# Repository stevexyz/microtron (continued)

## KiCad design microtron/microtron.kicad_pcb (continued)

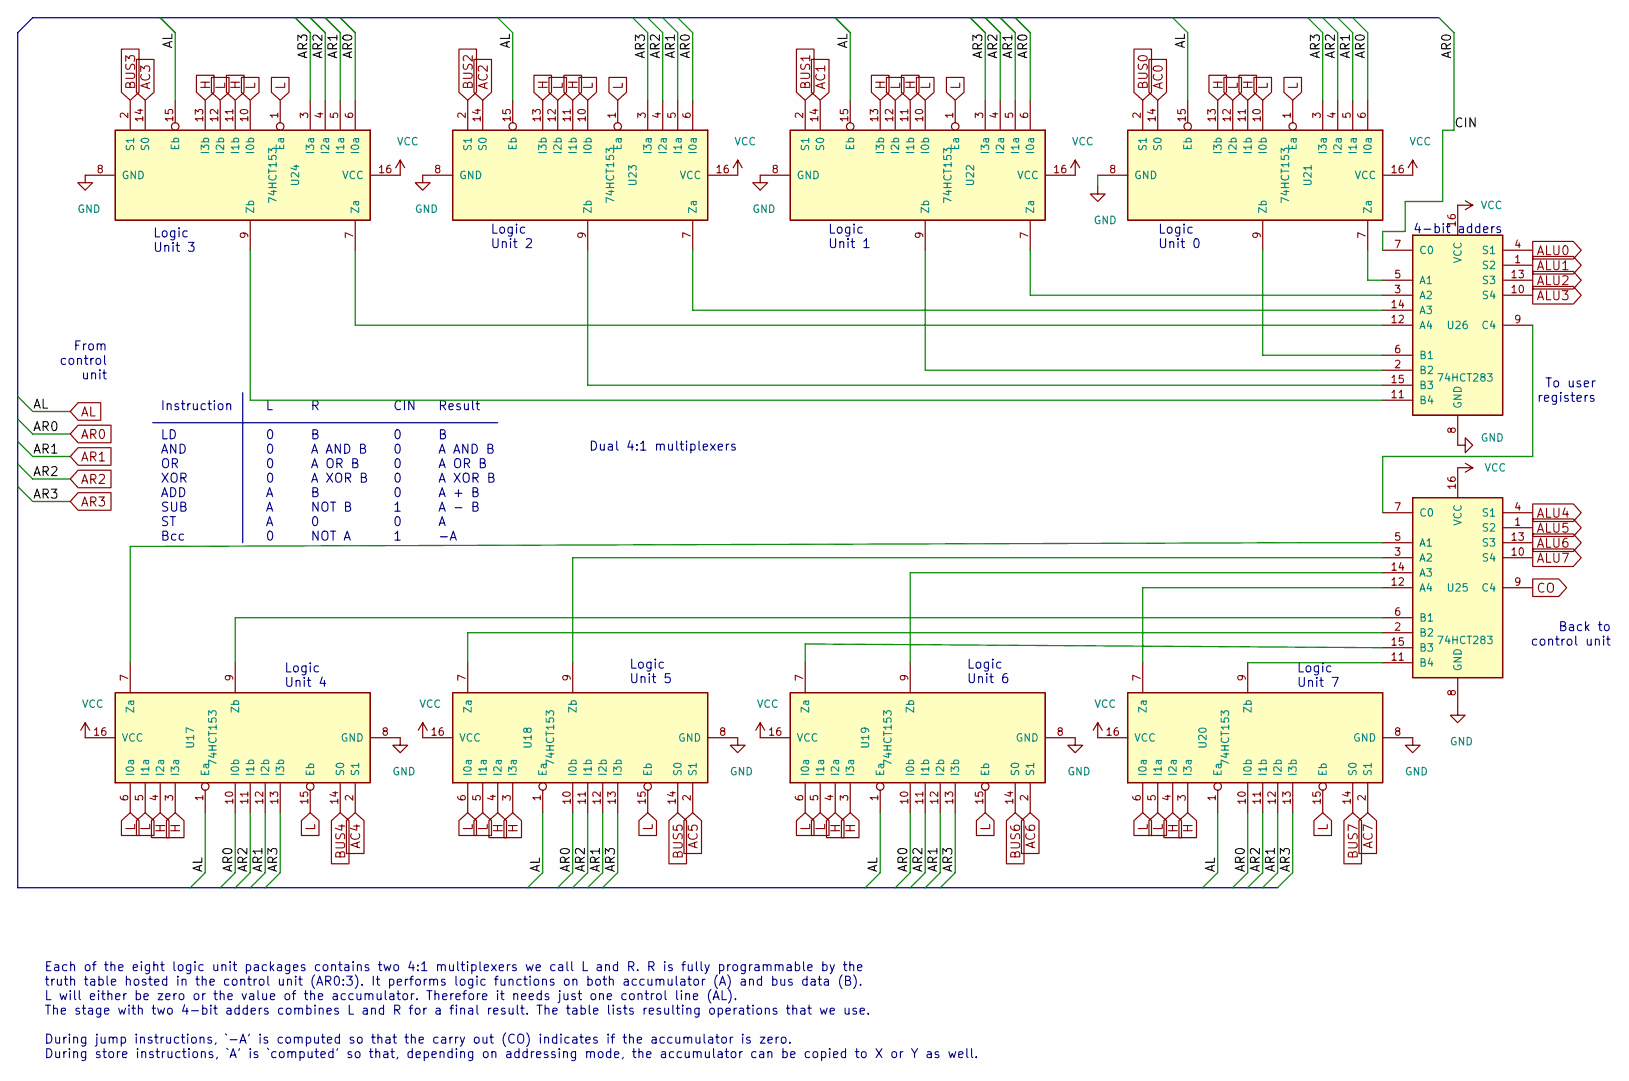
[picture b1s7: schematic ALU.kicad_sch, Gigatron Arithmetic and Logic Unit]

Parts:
U17, U18, U19, U20, U21, U22, U23, U24: 74HCT153; DIP-16_W7.62mm
U25, U26: 74HCT283; DIP-16_W7.62mm

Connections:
AC0: U21.14 (S0); also elsewhere on the board
AC1: U22.14 (S0); also elsewhere on the board
AC2: U23.14 (S0); also elsewhere on the board
AC3: U24.14 (S0); also elsewhere on the board
AC4: U17.2 (S1); also elsewhere on the board
AC5: U18.2 (S1); also elsewhere on the board
AC6: U19.2 (S1); also elsewhere on the board
AC7: U20.2 (S1); also elsewhere on the board
AL: U17.1 (Ea), U18.1 (Ea), U19.1 (Ea), U20.1 (Ea), U21.15 (Eb), U22.15 (Eb), U23.15 (Eb), U24.15 (Eb); also elsewhere on the board
ALU0: U26.4 (S1); also elsewhere on the board
ALU1: U26.1 (S2); also elsewhere on the board
ALU2: U26.13 (S3); also elsewhere on the board
ALU3: U26.10 (S4); also elsewhere on the board
ALU4: U25.4 (S1); also elsewhere on the board
ALU5: U25.1 (S2); also elsewhere on the board
ALU6: U25.13 (S3); also elsewhere on the board
ALU7: U25.10 (S4); also elsewhere on the board
AR0: U17.10 (I0b), U18.10 (I0b), U19.10 (I0b), U20.10 (I0b), U21.6 (I0a), U22.6 (I0a), U23.6 (I0a), U24.6 (I0a), U26.7 (C0); also elsewhere on the board
AR1: U17.12 (I2b), U18.12 (I2b), U19.12 (I2b), U20.12 (I2b), U21.5 (I1a), U22.5 (I1a), U23.5 (I1a), U24.5 (I1a); also elsewhere on the board
AR2: U17.11 (I1b), U18.11 (I1b), U19.11 (I1b), U20.11 (I1b), U21.4 (I2a), U22.4 (I2a), U23.4 (I2a), U24.4 (I2a); also elsewhere on the board
AR3: U17.13 (I3b), U18.13 (I3b), U19.13 (I3b), U20.13 (I3b), U21.3 (I3a), U22.3 (I3a), U23.3 (I3a), U24.3 (I3a); also elsewhere on the board
BUS0: U21.2 (S1); also elsewhere on the board
BUS1: U22.2 (S1); also elsewhere on the board
BUS2: U23.2 (S1); also elsewhere on the board
BUS3: U24.2 (S1); also elsewhere on the board
BUS4: U17.14 (S0); also elsewhere on the board
BUS5: U18.14 (S0); also elsewhere on the board
BUS6: U19.14 (S0); also elsewhere on the board
BUS7: U20.14 (S0); also elsewhere on the board
CO: U25.9 (C4); also elsewhere on the board
GND: U17.8 (GND), U18.8 (GND), U19.8 (GND), U20.8 (GND), U21.8 (GND), U22.8 (GND), U23.8 (GND), U24.8 (GND), U25.8 (GND), U26.8 (GND); also elsewhere on the board
H: U17.3 (I3a), U17.4 (I2a), U18.3 (I3a), U18.4 (I2a), U19.3 (I3a), U19.4 (I2a), U20.3 (I3a), U20.4 (I2a), U21.11 (I1b), U21.13 (I3b), U22.11 (I1b), U22.13 (I3b), U23.11 (I1b), U23.13 (I3b), U24.11 (I1b), U24.13 (I3b); also elsewhere on the board
L: U17.5 (I1a), U17.6 (I0a), U17.15 (Eb), U18.5 (I1a), U18.6 (I0a), U18.15 (Eb), U19.5 (I1a), U19.6 (I0a), U19.15 (Eb), U20.5 (I1a), U20.6 (I0a), U20.15 (Eb), U21.1 (Ea), U21.10 (I0b), U21.12 (I2b), U22.1 (Ea), U22.10 (I0b), U22.12 (I2b), U23.1 (Ea), U23.10 (I0b), U23.12 (I2b), U24.1 (Ea), U24.10 (I0b), U24.12 (I2b); also elsewhere on the board
unnamed: U17.7 (Za), U25.5 (A1)
unnamed: U17.9 (Zb), U25.6 (B1)
unnamed: U18.7 (Za), U25.2 (B2)
unnamed: U18.9 (Zb), U25.3 (A2)
unnamed: U19.7 (Za), U25.15 (B3)
unnamed: U19.9 (Zb), U25.14 (A3)
unnamed: U20.7 (Za), U25.12 (A4)
unnamed: U20.9 (Zb), U25.11 (B4)
unnamed: U21.7 (Za), U26.5 (A1)
unnamed: U21.9 (Zb), U26.6 (B1)
unnamed: U22.7 (Za), U26.3 (A2)
unnamed: U22.9 (Zb), U26.2 (B2)
unnamed: U23.7 (Za), U26.14 (A3)
unnamed: U23.9 (Zb), U26.15 (B3)
unnamed: U24.7 (Za), U26.12 (A4)
unnamed: U24.9 (Zb), U26.11 (B4)
unnamed: U25.7 (C0), U26.9 (C4)
VCC: U17.16 (VCC), U18.16 (VCC), U19.16 (VCC), U20.16 (VCC), U21.16 (VCC), U22.16 (VCC), U23.16 (VCC), U24.16 (VCC), U25.16 (VCC), U26.16 (VCC); also elsewhere on the board

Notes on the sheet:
Logic Unit 7
Back to control unit
Logic Unit 1
Logic Unit 0
Dual 4:1 multiplexers
Result B A AND B A OR B A XOR B A + B A - B A -A
Logic Unit 6
Logic Unit 2
From control unit
Instruction LD AND OR XOR ADD SUB ST Bcc
R B A AND B A OR B A XOR B B NOT B 0 NOT A
CIN 0 0 0 0 0 1 0 1
Logic Unit 4
Each of the eight logic unit packages contains two 4:1 multiplexers we call L and R. R is fully programmable by the truth table hosted in the control unit (AR0:3). It performs logic functions on both accumulator (A) and bus data (B). L will either be zero or the value of the accumulator. Therefore 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
To user registers
L 0 0 0 0 A A A 0
Logic Unit 5
4-bit adders
Logic Unit 3

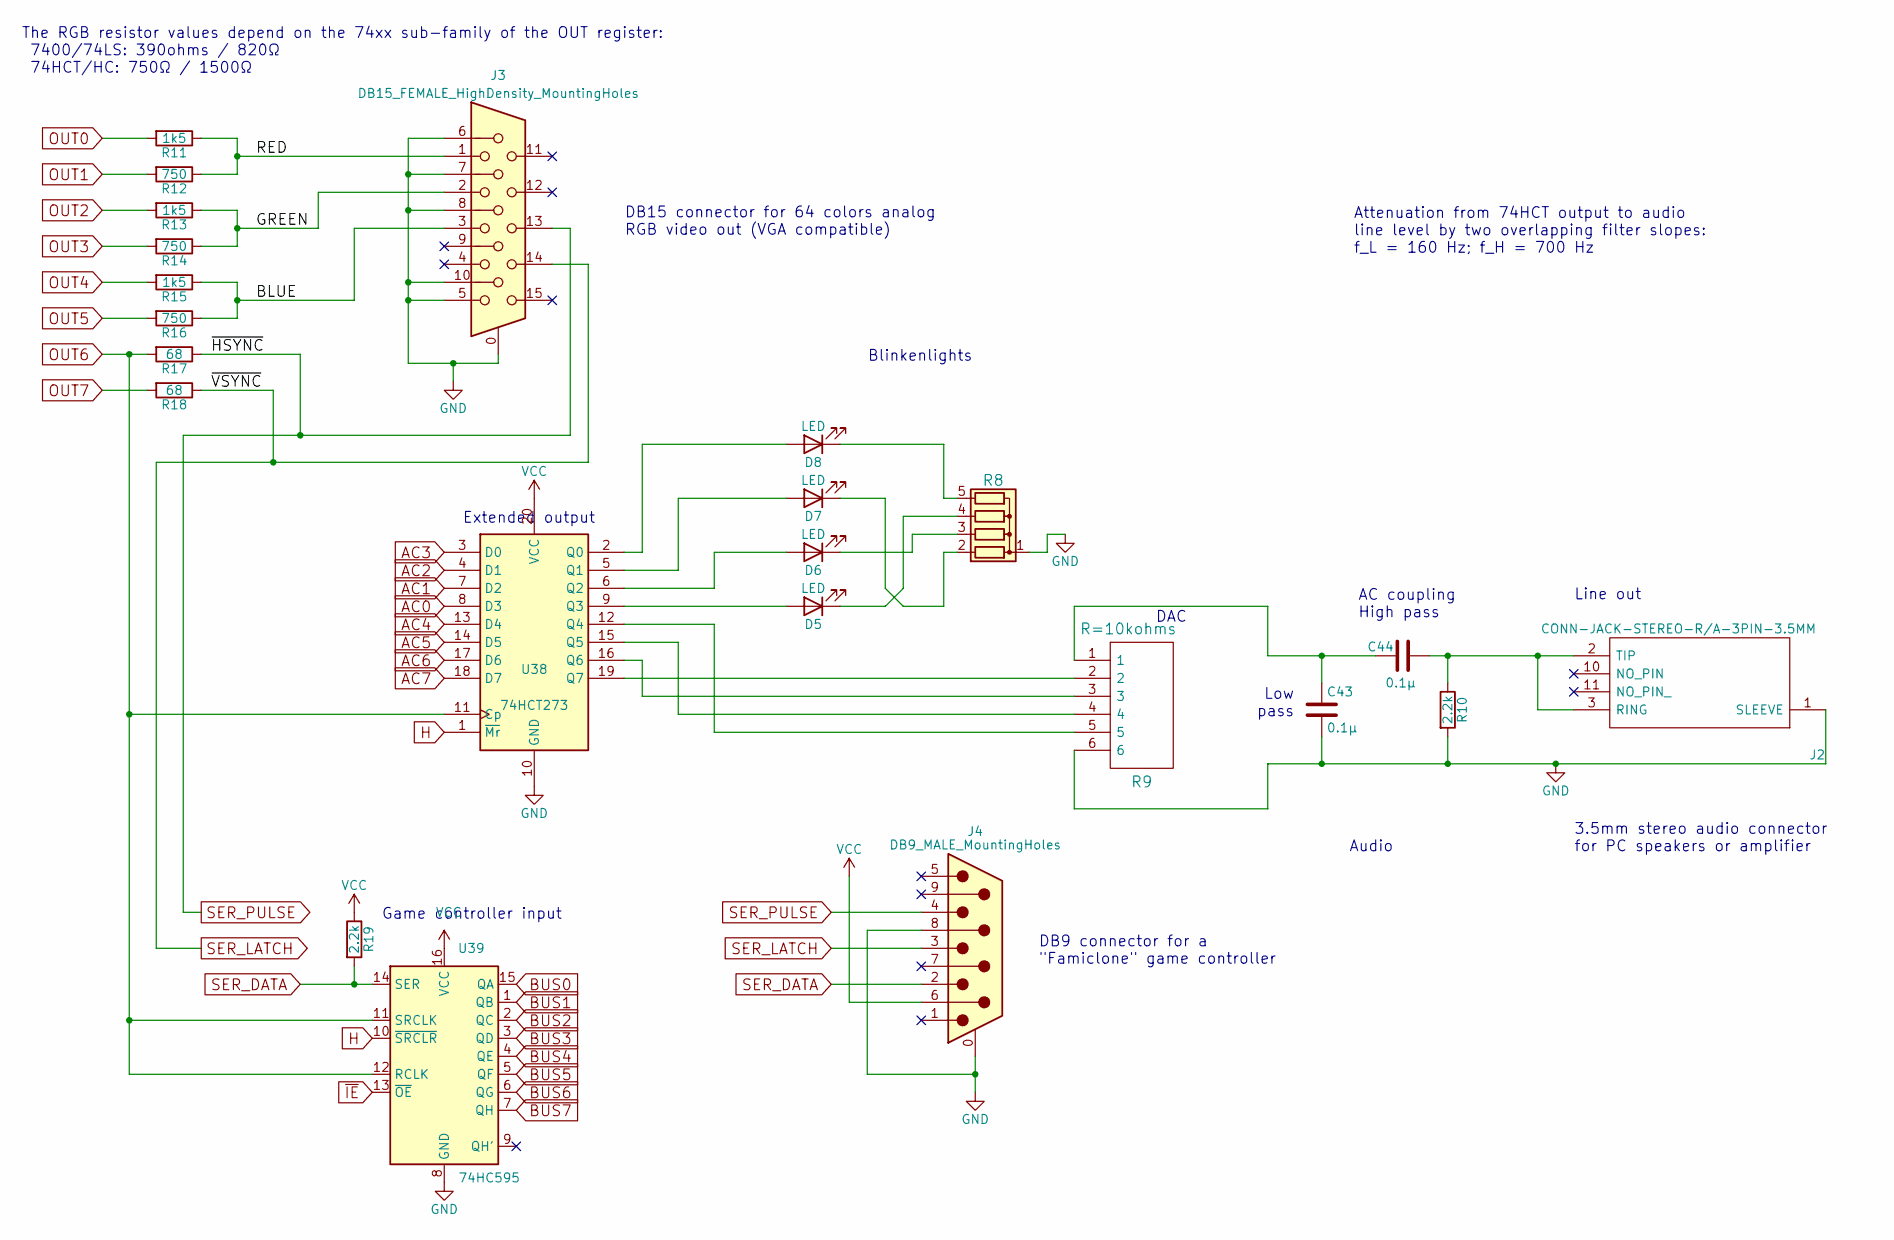
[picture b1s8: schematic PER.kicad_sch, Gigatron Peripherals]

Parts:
C43, C44: 0.1µ; C_Disc_D4.3mm_W1.9mm_P5.00mm
D5, D6, D7, D8: LED; LED_D3.0mm
J2: CONN-JACK-STEREO-R/A-3PIN-3.5MM; SJ13523N
J3: DB15_FEMALE_HighDensity_MountingHoles; DSUB-15-HD_Female_Horizontal_P2.29x1.98mm_EdgePinOffset3.03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
J4: DB9_MALE_MountingHoles; DSUB-9_Female_Horizontal_P2.77x2.84mm_EdgePinOffset4.94mm_H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
R8: 4605X-101-222LF; R_Array_SIP5
R9: R=10kohms; R_Array_SIP6
R10, R19: 2.2k; R_Axial_DIN0207_L6.3mm_D2.5mm_P10.16mm_Horizontal
R11, R13, R15: 1k5; R_Axial_DIN0207_L6.3mm_D2.5mm_P10.16mm_Horizontal
R12, R14, R16: 750; R_Axial_DIN0207_L6.3mm_D2.5mm_P10.16mm_Horizontal
R17, R18: 68; R_Axial_DIN0207_L6.3mm_D2.5mm_P10.16mm_Horizontal
U38: 74HCT273; DIP-20_W7.62mm
U39: 74HC595; DIP-16_W7.62mm

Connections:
/PER/BLUE: J3.3, R15.1, R16.1
/PER/GREEN: J3.2, R13.1, R14.1
/PER/RED: J3.1, R11.1, R12.1
AC0: U38.8 (D3); also elsewhere on the board
AC1: U38.7 (D2); also elsewhere on the board
AC2: U38.4 (D1); also elsewhere on the board
AC3: U38.3 (D0); also elsewhere on the board
AC4: U38.13 (D4); also elsewhere on the board
AC5: U38.14 (D5); also elsewhere on the board
AC6: U38.17 (D6); also elsewhere on the board
AC7: U38.18 (D7); also elsewhere on the board
BUS0: U39.15 (QA); also elsewhere on the board
BUS1: U39.1 (QB); also elsewhere on the board
BUS2: U39.2 (QC); also elsewhere on the board
BUS3: U39.3 (QD); also elsewhere on the board
BUS4: U39.4 (QE); also elsewhere on the board
BUS5: U39.5 (QF); also elsewhere on the board
BUS6: U39.6 (QG); also elsewhere on the board
BUS7: U39.7 (QH); also elsewhere on the board
GND: C43.2, J2.1 (SLEEVE), J3.0, J3.5, J3.6, J3.7, J3.8, J3.10, J4.0 (PAD), J4.8, R8.1 (common), R9.6, R10.2, U38.10 (GND), U39.8 (GND); also elsewhere on the board
H: U38.1 (~Mr), U39.10 (~SRCLR); also elsewhere on the board
unnamed: C43.1, C44.2, R9.1
unnamed: C44.1, J2.2 (TIP), J2.3 (RING), R10.1
unnamed: D5.1 (K), R8.4 (R3)
unnamed: D5.2 (A), U38.9 (Q3)
unnamed: D6.1 (K), R8.3 (R2)
unnamed: D6.2 (A), U38.6 (Q2)
unnamed: D7.1 (K), R8.2 (R1)
unnamed: D7.2 (A), U38.5 (Q1)
unnamed: D8.1 (K), R8.5 (R4)
unnamed: D8.2 (A), U38.2 (Q0)
unnamed: R9.2, U38.19 (Q7)
unnamed: R9.3, U38.16 (Q6)
unnamed: R9.4, U38.15 (Q5)
unnamed: R9.5, U38.12 (Q4)
OUT0: R11.2; also elsewhere on the board
OUT1: R12.2; also elsewhere on the board
OUT2: R13.2; also elsewhere on the board
OUT3: R14.2; also elsewhere on the board
OUT4: R15.2; also elsewhere on the board
OUT5: R16.2; also elsewhere on the board
OUT6: R17.2, U38.11 (Cp), U39.11 (SRCLK), U39.12 (RCLK); also elsewhere on the board
OUT7: R18.2; also elsewhere on the board
SER_DATA: J4.2, R19.2, U39.14 (SER)
SER_LATCH: J3.14, J4.3, R18.1
SER_PULSE: J3.13, J4.4, R17.1
VCC: J4.6, R19.1, U38.20 (VCC), U39.16 (VCC); also elsewhere on the board
~IE: U39.13 (~OE); also elsewhere on the board

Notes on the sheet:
DB15 connector for 64 colors analog RGB video out (VGA compatible)
DAC
Blinkenlights
Game controller input
Attenuation from 74HCT output to audio line level by two overlapping filter slopes: f_L = 160 Hz; f_H = 700 Hz
The RGB resistor values depend on the 74xx sub-family of the OUT register: 7400/74LS: 390ohms / 820Ω 74HCT/HC: 750Ω / 1500Ω
Audio
3.5mm stereo audio connector for PC speakers or amplifier
AC coupling High pass
Low pass
DB9 connector for a "Famiclone" game controller
Line out
Extended output

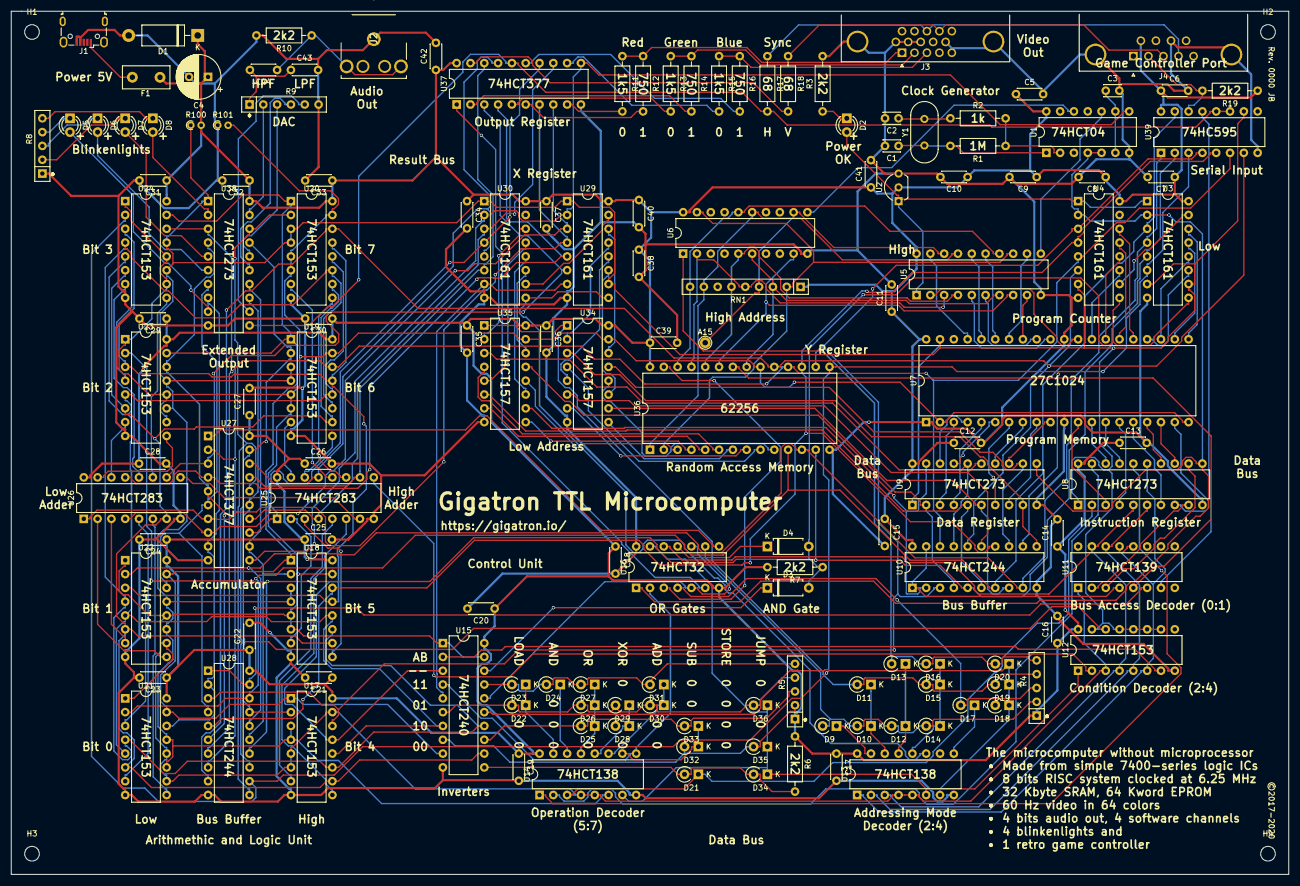
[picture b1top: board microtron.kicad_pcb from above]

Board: 2 copper layers, 234.9 x 158.8 mm, 149 parts (0 on the bottom side), 202 nets.

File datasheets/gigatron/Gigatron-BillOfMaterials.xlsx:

Gigatron Bill of Materials
https://gigatron.io/
Copyright © 2020 Walter Belgers
This Gigatron Bill of Materials is provided "as-is"
and licensed under CC BY-SA 4.0.
To view a copy of this license, visit
https://creativecommons.org/licenses/by-sa/4.0
 |  |  |  |  |  |  |  |  |  |  |  |  |  |  |  |  |  |  |  |  |  |  |  |  |  |  |  |  |  |  |  |  |  |  |  |  |  |  |  |  |  |  |  |  |  |  |  |  |  |  |  |  |  |  |  | TTL microcomputer
Function/module | Description | Part/value | On PCB | Per kit | Part URL (e.g.)
Clock | 47pF ceramic disc capacitor, radial | Code 47 | C1-C3 | 3 | https://www.digikey.nl/product-detail/en/vishay-bc-component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
Power | 220uF polarized radial input cap | Panasonic EEU-FC1E221 | C4 | 1 | https://nl.farnell.com/panasonic/eeu-fc1e221/cap-220-f-25v-2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
Power, Audio | 100nF ceramic disc | Code 104 | C5-C44 | 40 | https://www.digikey.nl/product-detail/en/vishay-bc-component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
Power | Zener diode 5.6V/5W | 1N5339B, DO-15 | D1 | 1 | https://nl.mouser.com/ProductDetail/Micro-Commercial-Compone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
Power, Blinkenlights | LED (red) | 1.8V, 2mA, 3.15mm | D2, D5-D8 | 5 | https://www.digikey.com/product-detail/en/everlight-electron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
Control unit | Signaling diode | 1N60P or BAT42 compatible, DO-35 | D3-D4,D9-D36 | 30 | https://nl.mouser.com/ProductDetail/Vishay-Semiconductors/BA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
Power | Multifuse 60V/0.75A/180mΩ | MF-R075-ND | F1 | 1 | https://www.digikey.nl/product-detail/en/bourns-inc/MF-R075/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
Power | Mini-USB receptacle | 54819-0519 | J1 | 1 | http://nl.farnell.com/molex/54819-0519/mini-usb-2-0-otg-type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
Audio | 3.5 mm audio jack | SJ-352{345}N | J2 | 1 | https://www.digikey.nl/product-detail/en/cui-inc/SJ1-3523N/C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
Video | 15pin D-SUB female receptacle | L77HDE15SD1CH4R | J3 | 1 | http://uk.farnell.com/amphenol/l77hde15sd1ch4r/connector-hd-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
Game controller | 9pin D-SUB male receptacle | 5747840-3 | J4 | 1 | https://www.digikey.nl/product-detail/en/te-connectivity-amp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
Clock | Feedback resistor | 1M | R1 | 1 | https://www.digikey.nl/product-detail/en/stackpole-electroni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
Clock | Damping resistor | 1k | R2 | 1 | https://www.digikey.nl/product-detail/en/stackpole-electroni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
Power, Control unit, Audio, Input | Resistor 2.2kΩ | 2.2k | R3,R6-R7,R10,R19 | 5 | https://www.digikey.nl/product-detail/en/stackpole-electroni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
Controll unit, Blinkenlights | 5-pin resistor array, 2.2kΩ | 4605X-101-222LF | R4-R5,R8 | 3 | https://nl.mouser.com/ProductDetail/Bourns/4605X-101-222LF?q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
Audio | 6-pin R2R netwerk, 10kΩ | 4606X-R2R-103LF | R9 | 1 | https://nl.mouser.com/ProductDetail/Bourns/4606X-R2R-103LF/?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
Video | DAC resistor | 1.5k | R11,R13,R15 | 3 | https://www.digikey.nl/product-detail/en/stackpole-electroni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
Video | DAC resistor | 750 | R12,R14,R16 | 3 | https://www.digikey.nl/product-detail/en/stackpole-electroni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
Video | Terminator HS/VS lines | 68 | R17-R18 | 2 | https://www.digikey.nl/product-detail/en/stackpole-electroni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
Clock | Hex inverter (74HCT) | 74HCT04 | U1 | 1 | http://eu.mouser.com/ProductDetail/Texas-Instruments/SN74HCT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
Power | Supervisory circuit. Power-on Reset | MCP100-450DI/TO | U2 | 1 | https://www.digikey.nl/products/en?keywords=MCP100-450DI
Program Counter, X register | 4-bit presettable counter '161/'163 | 74HCT161 | U3-U6,U29-U30 | 6 | https://nl.mouser.com/Search/ProductDetail.aspx?R=CD74HCT161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
Program ROM | EPROM 1Mb (64Kx16) | 27C1024, ≤150ns | U7 | 1 | https://nl.mouser.com/ProductDetail/Microchip-Technology-Atm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
IR,D,XOUT registers | 8-bit D-type register | 74HCT273 | U8-U9,U38 | 3 | https://nl.mouser.com/ProductDetail/Texas-Instruments/SN74HC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
Databus en input | Octal bus driver non-inv | 74HCT244 | U10,U28 | 2 | https://nl.mouser.com/ProductDetail/Texas-Instruments/SN74HC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
Control unit | Dual 2-to-4 decoder | 74HCT139 | U11 | 1 | https://nl.farnell.com/texas-instruments/sn74hct139n/logic-d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
Control unit, ALU | Dual 4-to-1 multiplexer | 74HCT153 | U12,U17-U24 | 9 | https://nl.mouser.com/ProductDetail/Texas-Instruments/CD74HC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
Control unit | 3-to-8 decoder | 74HCT138 | U13-U14 | 2 | https://nl.farnell.com/texas-instruments/sn74hct138n/ic-deco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
Control unit | Octal inverting buffer | 74HCT240 | U15 | 1 | https://nl.farnell.com/texas-instruments/sn74hct240n/octal-b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
Control unit | Quad 2-input OR | 74HCT32 | U16 | 1 | https://nl.mouser.com/ProductDetail/Texas-Instruments/CD74HC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
ALU | 4-bit adder | 74HCT283 | U25-U26 | 2 | https://nl.mouser.com/ProductDetail/Texas-Instruments/CD74HC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
AC, OUT and Y registers | Octal D-type flip-flops with common enable | 74HCT377 | U27,U31,U37 | 3 | https://www.digikey.nl/product-detail/en/texas-instruments/S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
Address unit | Quad 2-to-1 line data selector | 74HCT157 | U32-U35 | 4 | https://www.digikey.nl/product-detail/en/texas-instruments/S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
Data RAM | SRAM 32k x 8, 55ns | 62256 | U36 | 1 | http://nl.farnell.com/lyontek/ly62256pl-55lli/sram-256k-32kx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
Input register | 8-bit shift register with 3-state output | 74HC595 | U39 | 1 | http://eu.mouser.com/ProductDetail/Texas-Instruments/SN74HC5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
Clock | 6.25MHz/30pF crystal | MP062-E | Y1 | 1 | http://eu.mouser.com/Search/ProductDetail.aspx?R=MP062-Evirt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
Interconnect | Printed Circuit Board (PCB) | green, lead-free HASL | - | 1 | your favourite PCB manufacturer
Power | USB cable | AWG28 | - | 1 | https://nl.mouser.com/ProductDetail/562-3021055-03
Program ROM | UV protection label | 25.4mm x 10mm | - | 1 | https://uk.farnell.com/te-connectivity/12100/label-eprom-pcb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
IC sockets | IC socket | 40-pin DIP | - | 1 | https://www.digikey.nl/product-detail/en/on-shore-technology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
IC sockets | IC socket | 28-pin DIP | - | 1 | https://www.digikey.nl/product-detail/en/assmann-wsw-compone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
Game controller | Prefab gamepad, famicom clone | DB9 serial | - | 1 | https://nl.aliexpress.com/item/32819985527.html
Enclosure | Wooden casing with plexiglass |  | - | 1 | custom made, no longer available
Enclosure | Little rubber feet (bumpons) | SJ-5302 (7.9mm) | - | 8 | https://nl.mouser.com/ProductDetail/3M-Electronic-Specialty/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
Manual | Full-colour paper manual | Wire-O, plastic cover | - | 1 | local copy shop
Pluggy McPlugface | Printed Circuit Board (PCB) | green, lead-free HASL | - | 1 | your favourite PCB manufacturer
Pluggy McPlugface | PS/2 receptacle | mini-DIN 6 pins | J1 | 1 | https://nl.mouser.com/ProductDetail/Kycon/KMDGX-6S-AS?qs=%2F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
Pluggy McPlugface | 9pin D-SUB female receptacle | L77SDE09SOL2 | J2 | 1 | https://nl.mouser.com/ProductDetail/523-L77SDE09SOL2
Pluggy McPlugface | Microcontroller | ATtiny85 DIP-8 | U1 | 1 | http://www.mouser.com/ProductDetail/microchip/attiny85-20pu/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
Pluggy McPlugface | IC socket | 8-pin DIP | - | 1 | http://www.mouser.com/ProductDetail/mill-max/110-47-308-41-0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
EPROM content | https://github.com/kervinck/gigatron-rom
ATtiny content | https://github.com/kervinck/gigatron-rom/tree/master/Utils/B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
Assembly manual | https://gigatron.io/manual
Main PCB design files | https://gigatron.io/pcb
Pluggy PCB design files | https://gigatron.io/pluggy
20200623

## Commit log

2022-06-03 initial setup and replaced PCH in schematics
2022-06-03 removed Y multiplexers
2022-07-18 removed PCH incrementer and routed PCB
2022-07-18 cleanup
